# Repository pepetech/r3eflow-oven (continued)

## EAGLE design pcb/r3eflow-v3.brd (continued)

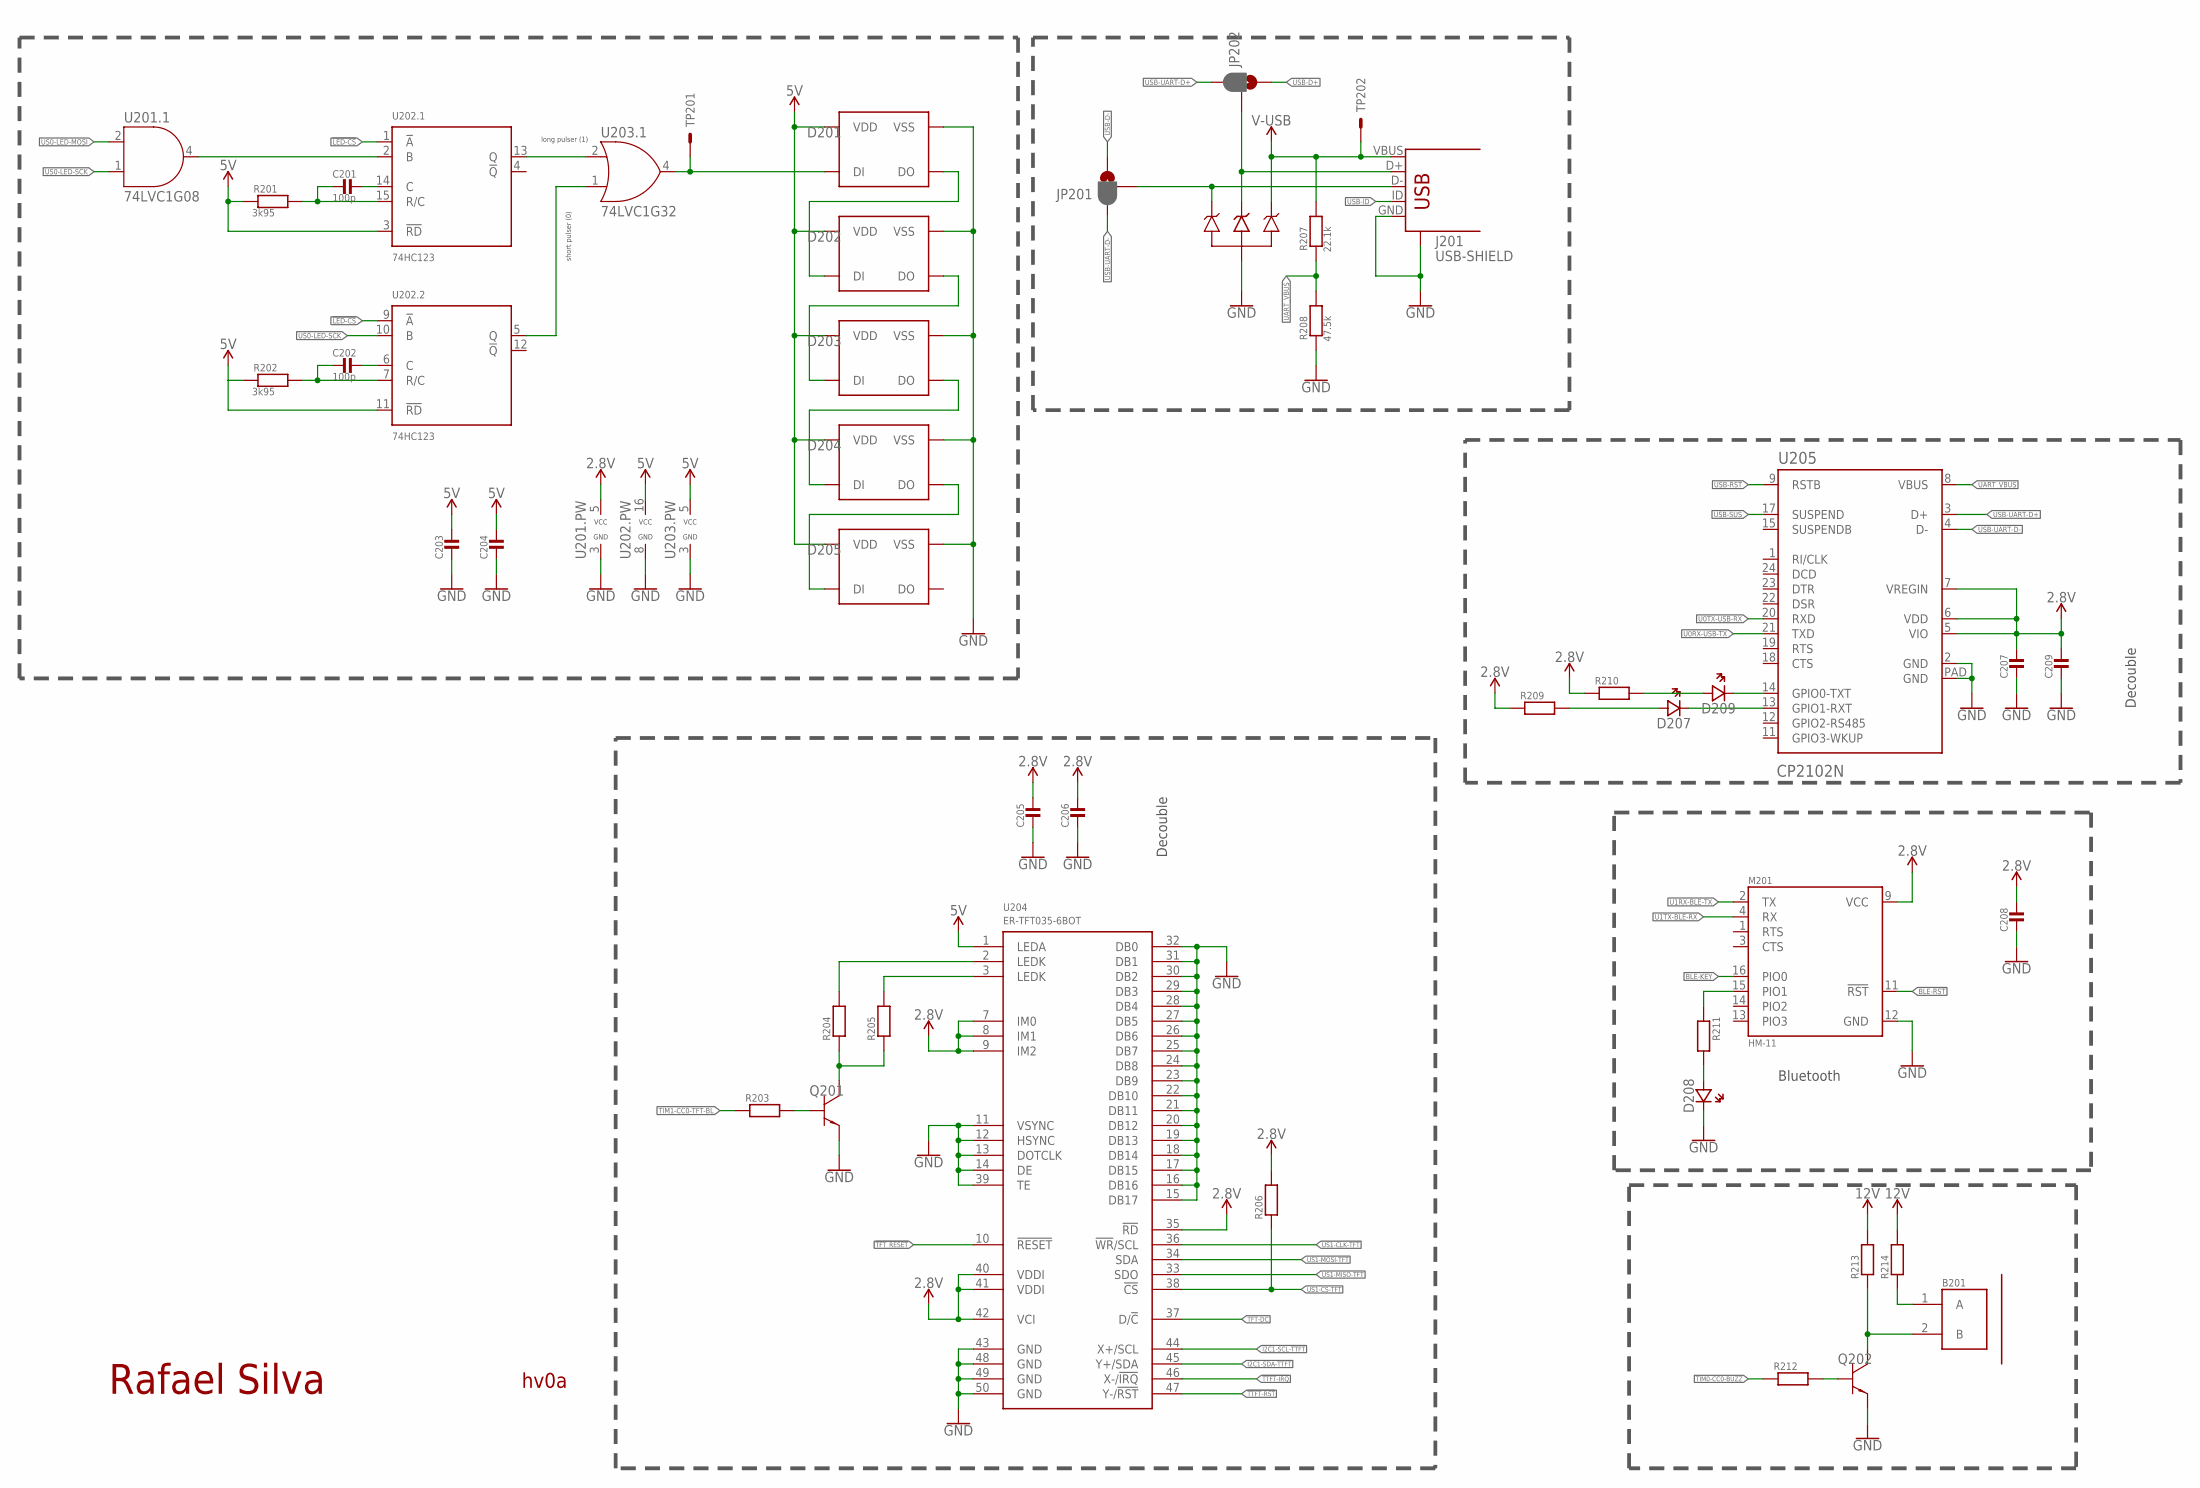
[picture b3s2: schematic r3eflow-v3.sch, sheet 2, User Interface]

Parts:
B201: PKLCS1212E2400-R1; BUZZ_PIEZO_SMD
C201, C202: 100p; 0603_WAVE
C203, C204, C205, C206, C207, C208, C209: MLCC0603; 0603_WAVE
D201, D202, D203, D204, D205: WS2812B; 3535
D206: SP0503BAHT; SOT143
D207, D208, D209: LED0603; CHIPLED_0603
J201: USB-SHIELD; USB-M-S1
JP201, JP202: JUMPER-SMT_3_1-NC_PASTE_SILK; SMT-JUMPER_3_1-NC_PASTE_SILK
M201: HM-11
Q201, Q202: BC817-40; SOT-23-3
R201, R202: 3k95; 0603_WAVE
R203, R204, R205, R206, R209, R210, R211, R212, R213, R214: RESISTOR0603; 0603_WAVE
R207: 22.1k; 0603_WAVE
R208: 47.5k; 0603_WAVE
TP201, TP202: TEST_POINT
U201: 74LVC1G08; SC-70-5
U202: 74HC123; TSSOP-16
U203: 74LVC1G32; SC-70-5
U204: ER-TFT035-6BOT; ZIF50-TFT_BACK
U205: CP2102N; QFN24

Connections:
2.8V: C205.P$1, C206.P$1, C207.P$1, C208.P$1, C209.P$1, M201.9 (VCC), R206.P$2, R209.P$1, R210.P$1, U201.5 (VCC), U204.7 (IM0), U204.8 (IM1), U204.9 (IM2), U204.35 (!RD), U204.40 (VDDI), U204.41 (VDDI), U204.42 (VCI), U205.5 (VIO), U205.6 (VDD), U205.7 (VREGIN); also elsewhere on the board
5V: C203.P$1, C204.P$1, D201.3 (VDD), D202.3 (VDD), D203.3 (VDD), D204.3 (VDD), D205.3 (VDD), R201.P$1, R202.P$1, U202.3 (!RD), U202.11 (!RD), U202.16 (VCC), U203.5 (VCC), U204.1 (LEDA); also elsewhere on the board
12V: R213.P$2, R214.P$2; also elsewhere on the board
!LED-CS: U202.1 (!A), U202.9 (!A); also elsewhere on the board
!TFT_RESET: U204.10 (!RESET); also elsewhere on the board
!TTFT-IRQ: U204.46 (X-/!IRQ!); also elsewhere on the board
!TTFT-RST: U204.47 (Y-/!RST!); also elsewhere on the board
BLE-!RST: M201.11 (!RST!); also elsewhere on the board
BLE-KEY: M201.16 (PIO0); also elsewhere on the board
D8-DI: D201.2 (DI), TP201.1, U203.4 (Y)
D8_DO: D201.4 (DO), D202.2 (DI)
D9-DO: D202.4 (DO), D203.2 (DI)
D10-DO: D203.4 (DO), D204.2 (DI)
D11-DO: D204.4 (DO), D205.2 (DI)
GND: C203.P$2, C204.P$2, C205.P$2, C206.P$2, C207.P$2, C208.P$2, C209.P$2, D201.1 (VSS), D202.1 (VSS), D203.1 (VSS), D204.1 (VSS), D205.1 (VSS), D206.1, D208.C (CA), J201.GND, J201.GND@1 (CASE), J201.GND@2 (CASE), J201.GND@3 (CASE), J201.GND@4 (CASE), M201.12 (GND), Q201.P$2 (EM2), Q202.P$2 (EM2), R208.P$1, U201.3 (GND), U202.8 (GND), U203.3 (GND), U204.11 (VSYNC), U204.12 (HSYNC), U204.13 (DOTCLK), U204.14 (DE), U204.15 (DB17), U204.16 (DB16), U204.17 (DB15), U204.18 (DB14), U204.19 (DB13), U204.20 (DB12), U204.21 (DB11), U204.22 (DB10), U204.23 (DB9), U204.24 (DB8), U204.25 (DB7), U204.26 (DB6), U204.27 (DB5), U204.28 (DB4), U204.29 (DB3), U204.30 (DB2), U204.31 (DB1), U204.32 (DB0), U204.39 (TE), U204.43 (GND), U204.48 (GND), U204.49 (GND), U204.50 (GND), U205.2 (GND), U205.PAD (GND); also elsewhere on the board
I2C1-SCL-TTFT: U204.44 (X+/SCL); also elsewhere on the board
I2C1-SDA-TTFT: U204.45 (Y+/SDA); also elsewhere on the board
unnamed: B201.1 (A), R214.P$1
unnamed: D207.C (CA), U205.13 (GPIO1-RXT)
unnamed: D209.C (CA), U205.14 (GPIO0-TXT)
unnamed: D209.A (AN), R210.P$2
unnamed: B201.2 (B), Q202.P$3 (C03), R213.P$1
unnamed: Q202.P$1 (BA1), R212.P$2
unnamed: D207.A (AN), R209.P$2
unnamed: Q201.P$1 (BA1), R203.P$2
unnamed: D208.A (AN), R211.P$2
unnamed: M201.15 (PIO1), R211.P$1
unnamed: U202.5 (Q), U203.1 (B)
unnamed: U202.13 (Q), U203.2 (A)
unnamed: U201.4 (Y), U202.2 (B)
unnamed: D206.3, J201.D+, JP202.2
unnamed: D206.2, J201.D-, JP201.2
TFT-DC: U204.37 (D/!C!); also elsewhere on the board
TFT-LEDK: Q201.P$3 (C03), R204.P$1, R205.P$1
TFT-LEDK1: R204.P$2, U204.2 (LEDK)
TFT-LEDK2: R205.P$2, U204.3 (LEDK)
TIM0-CC0-BUZZ: R212.P$1; also elsewhere on the board
TIM1-CC0-TFT-BL: R203.P$1; also elsewhere on the board
U0RX-USB-TX: U205.21 (TXD); also elsewhere on the board
U0TX-USB-RX: U205.20 (RXD); also elsewhere on the board
U1RX-BLE-TX: M201.2 (TX); also elsewhere on the board
U1TX-BLE-RX: M201.4 (RX); also elsewhere on the board
U11.1-C: C201.P$1, U202.14 (C)
U11.1-RC: C201.P$2, R201.P$2, U202.15 (R/C)
U11.2-C: C202.P$1, U202.6 (C)
U11.2-RC: C202.P$2, R202.P$2, U202.7 (R/C)
UART_VBUS: R207.P$1, R208.P$2, U205.8 (VBUS)
US0-LED-MOSI: U201.2 (A); also elsewhere on the board
US0-LED-SCK: U201.1 (B), U202.10 (B); also elsewhere on the board
US1-CLK-TFT: U204.36 (!WR!/SCL); also elsewhere on the board
US1-CS-TFT: R206.P$1, U204.38 (!CS); also elsewhere on the board
US1-MISO-TFT: U204.33 (SDO); also elsewhere on the board
US1-MOSI-TFT: U204.34 (SDA); also elsewhere on the board
USB-D+: JP202.1; also elsewhere on the board
USB-D-: JP201.1; also elsewhere on the board
USB-ID: J201.ID; also elsewhere on the board
USB-RST: U205.9 (RSTB); also elsewhere on the board
USB-SUS: U205.17 (SUSPEND); also elsewhere on the board
USB-UART-D+: JP202.3, U205.3 (D+)
USB-UART-D-: JP201.3, U205.4 (D-)
V_USB: D206.4, J201.VBUS, R207.P$2, TP202.1

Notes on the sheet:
Decouble
Bluetooth
short pulser (0)
long pulser (1)

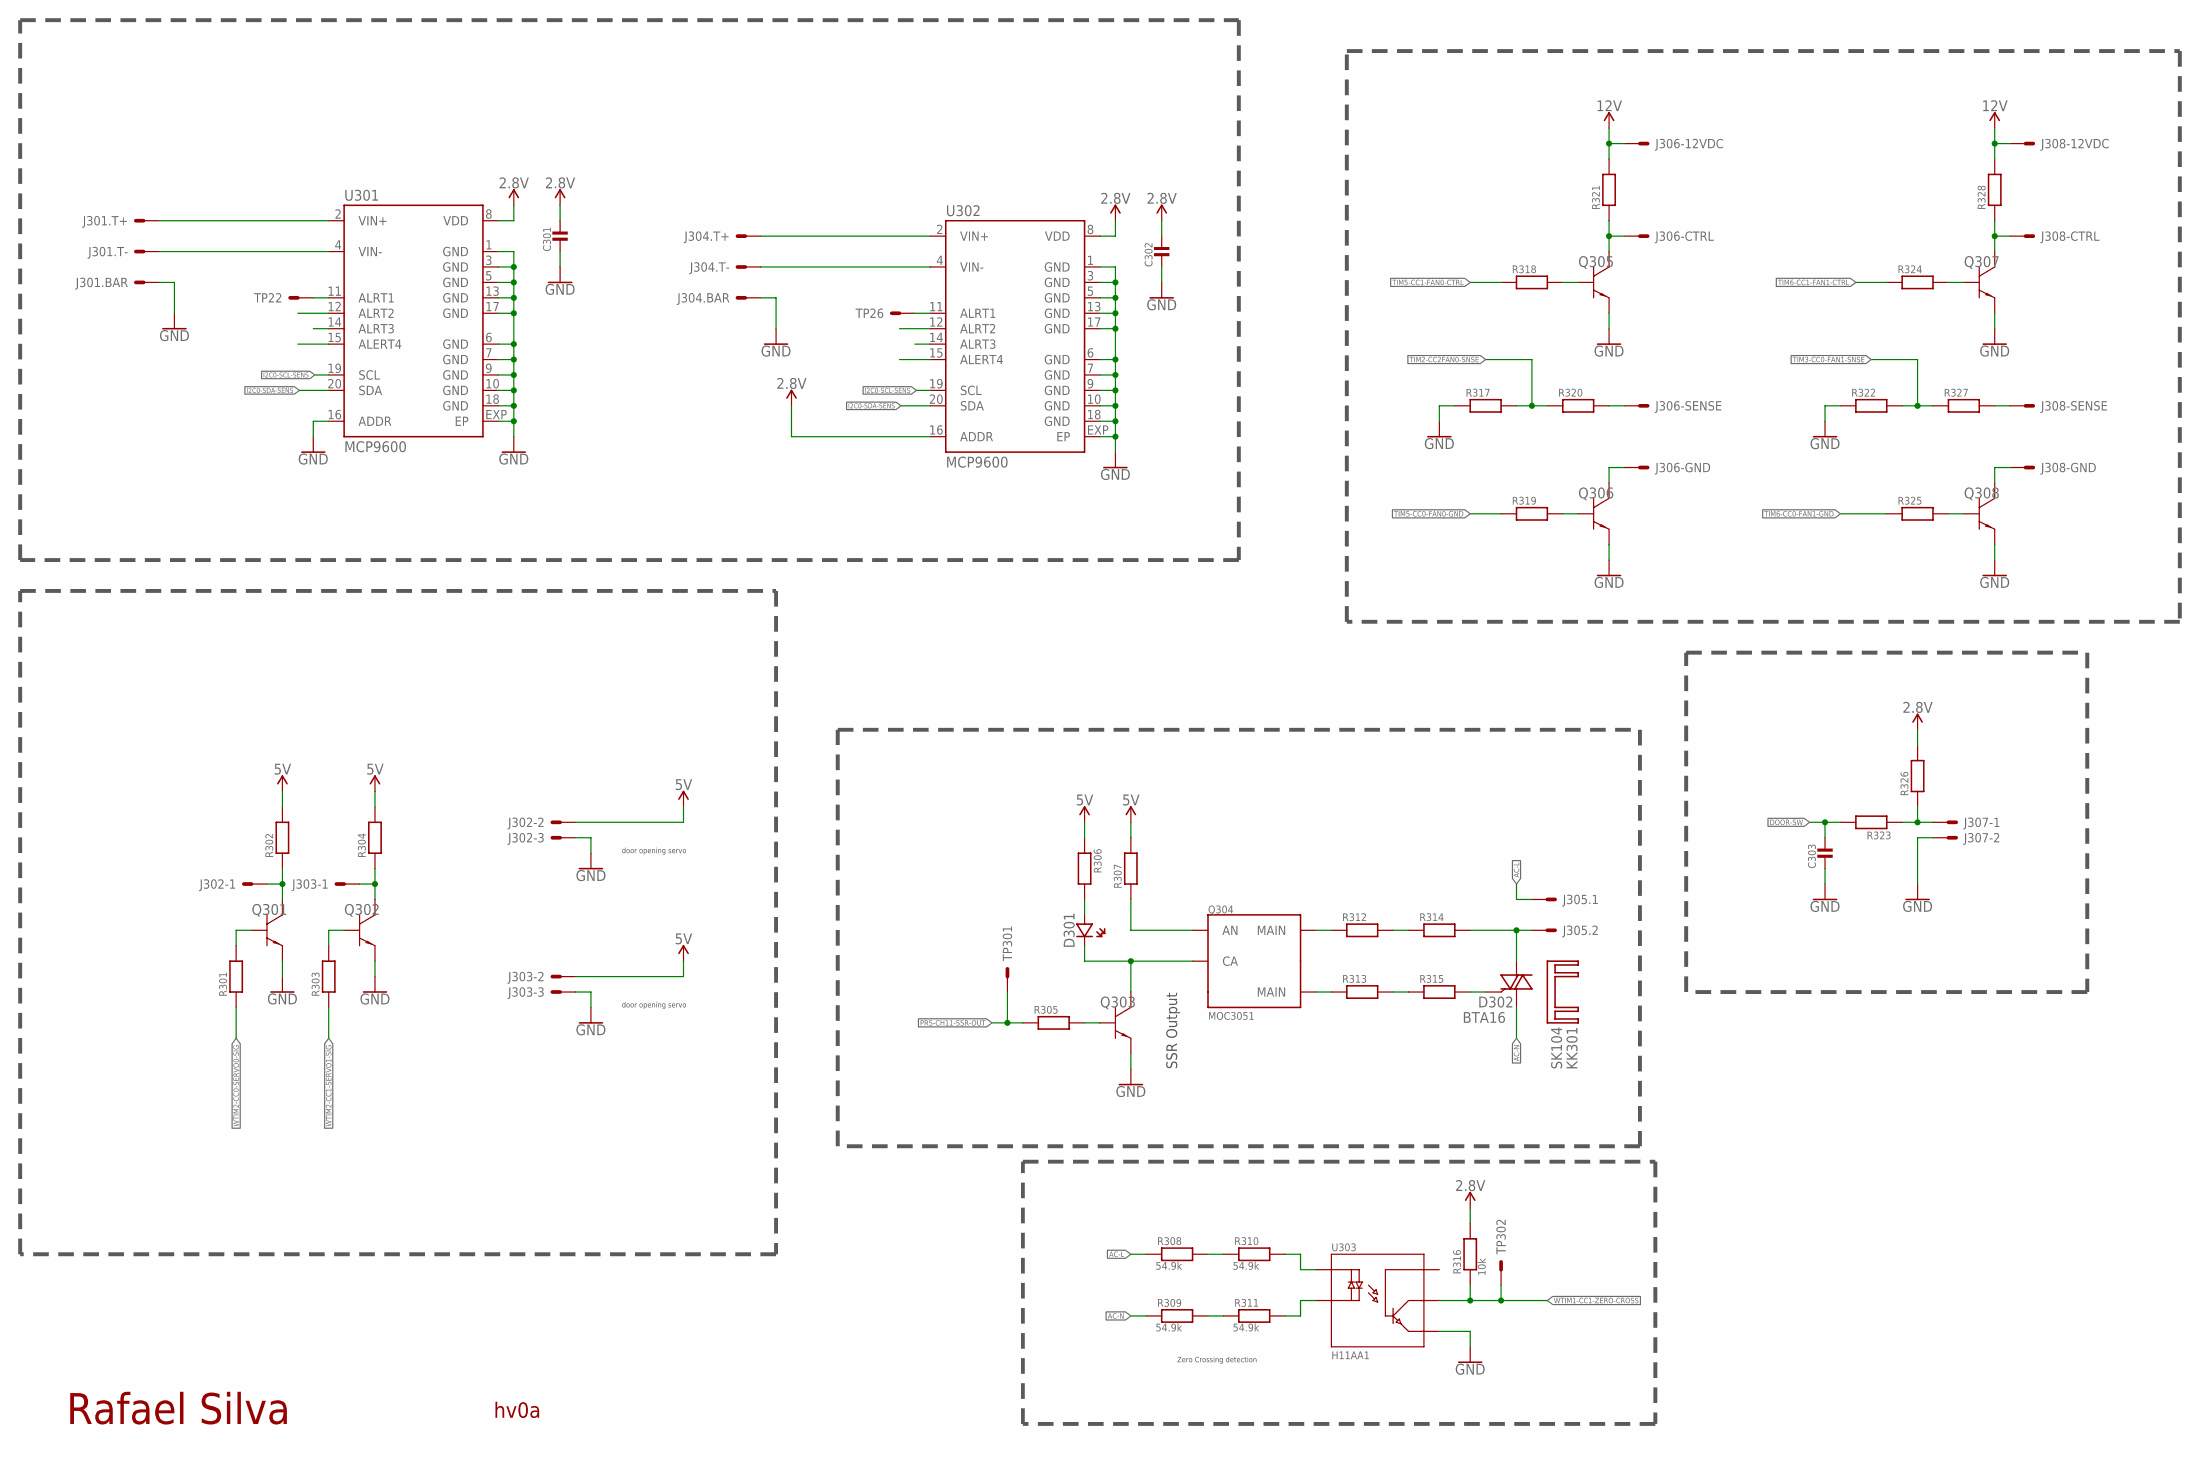
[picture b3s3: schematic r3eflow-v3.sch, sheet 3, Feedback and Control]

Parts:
C301, C302, C303: MLCC0603; 0603_WAVE
D301: LED0603; CHIPLED_0603
D302: BTA16; TO220DS
J301, J304: PCC-SMP
J302, J303: 3X1_2.54
J305: 2EDG-2P
J306, J308: 4P-PC-FAN; KF2510-3+1P
J307: 2X1_2.54
KK301: SK104
Q301, Q302, Q303, Q305, Q306, Q307, Q308: BC817-40; SOT-23-3
Q304: MOC3051; DIP-6-SMD
R301, R302, R303, R304, R305, R306, R307, R317, R318, R319, R320, R321, R322, R323, R324, R325, R326, R327, R328: RESISTOR0603; 0603_WAVE
R308, R309, R310, R311: 54.9k; _1206
R312, R313, R314, R315: RESISTOR_1206; _1206
R316: 10k; 0603_WAVE
TP22, TP26, TP301, TP302: TEST_POINT
U301, U302: MCP9600; TQFN20-5X5
U303: H11AA1; DIP-6-SMD

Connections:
2.8V: C301.P$1, C302.P$1, R316.P$2, R326.P$2, U301.8 (VDD), U302.8 (VDD), U302.16 (ADDR); also elsewhere on the board
5V: J302.P$2, J303.P$2, R302.P$2, R304.P$2, R306.P$1, R307.P$2; also elsewhere on the board
12V: J306.2, J308.2, R321.P$2, R328.P$2; also elsewhere on the board
AC-L: J305.P$1, R308.1; also elsewhere on the board
AC-N: D302.A1, R309.1; also elsewhere on the board
DOOR-SW: C303.P$1, R323.P$2; also elsewhere on the board
GND: C301.P$2, C302.P$2, C303.P$2, J301.3-BAR, J301.4-BAR, J302.P$3, J303.P$3, J304.3-BAR, J304.4-BAR, J307.2, Q301.P$2 (EM2), Q302.P$2 (EM2), Q303.P$2 (EM2), Q305.P$2 (EM2), Q306.P$2 (EM2), Q307.P$2 (EM2), Q308.P$2 (EM2), R317.P$1, R322.P$1, U301.1 (GND), U301.3 (GND), U301.5 (GND), U301.6 (GND), U301.7 (GND), U301.9 (GND), U301.10 (GND), U301.13 (GND), U301.16 (ADDR), U301.17 (GND), U301.18 (GND), U301.EXP (EP), U302.1 (GND), U302.3 (GND), U302.5 (GND), U302.6 (GND), U302.7 (GND), U302.9 (GND), U302.10 (GND), U302.13 (GND), U302.17 (GND), U302.18 (GND), U302.EXP (EP), U303.P$4 (E); also elsewhere on the board
I2C0-SCL-SENS: U301.19 (SCL), U302.19 (SCL); also elsewhere on the board
I2C0-SDA-SENS: U301.20 (SDA), U302.20 (SDA); also elsewhere on the board
unnamed: J307.1, R323.P$1, R326.P$1
unnamed: D302.A2, J305.P$2, R314.2
unnamed: Q303.P$1 (BA1), R305.P$2
unnamed: D301.C (CA), Q303.P$3 (C03), Q304.P$2 (CA)
unnamed: R308.2, R310.1
unnamed: R310.2, U303.P$1 (AC)
unnamed: R311.2, U303.P$2 (CA)
unnamed: R309.2, R311.1
unnamed: Q304.P$1 (AN), R307.P$1
unnamed: Q304.P$4 (MAIN), R312.1
unnamed: Q304.P$6 (MAIN), R313.1
unnamed: R312.2, R314.1
unnamed: R313.2, R315.1
unnamed: D302.G, R315.2
unnamed: Q301.P$1 (BA1), R301.P$2
unnamed: J302.P$1, Q301.P$3 (C03), R302.P$1
unnamed: D301.A (AN), R306.P$2
unnamed: J303.P$1, Q302.P$3 (C03), R304.P$1
unnamed: Q302.P$1 (BA1), R303.P$2
unnamed: Q306.P$1 (BA1), R319.P$2
unnamed: J306.1, Q306.P$3 (C03)
unnamed: Q305.P$1 (BA1), R318.P$2
unnamed: J306.4, Q305.P$3 (C03), R321.P$1
unnamed: Q308.P$1 (BA1), R325.P$2
unnamed: Q307.P$1 (BA1), R324.P$2
unnamed: J308.4, Q307.P$3 (C03), R328.P$1
unnamed: J308.1, Q308.P$3 (C03)
unnamed: J306.3, R320.P$2
unnamed: J308.3, R327.P$2
PRS-CH11-SSR-OUT: R305.P$1, TP301.1; also elsewhere on the board
TC_VIN0+: J301.1-T+, U301.2 (VIN+)
TC_VIN0-: J301.2-T-, U301.4 (VIN-)
TC_VIN1+: J304.1-T+, U302.2 (VIN+)
TC_VIN1-: J304.2-T-, U302.4 (VIN-)
TIM2-CC2FAN0-SNSE: R317.P$2, R320.P$1; also elsewhere on the board
TIM3-CC0-FAN1-SNSE: R322.P$2, R327.P$1; also elsewhere on the board
TIM5-CC0-FAN0-GND: R319.P$1; also elsewhere on the board
TIM5-CC1-FAN0-CTRL: R318.P$1; also elsewhere on the board
TIM6-CC0-FAN1-GND: R325.P$1; also elsewhere on the board
TIM6-CC1-FAN1-CTRL: R324.P$1; also elsewhere on the board
U4-ALRT1: TP22.1, U301.11 (ALRT1)
U4-ALRT2: U301.12 (ALRT2)
U4-ALRT3: U301.14 (ALRT3)
U4-ALRT4: U301.15 (ALERT4)
U7-ALRT1: TP26.1, U302.11 (ALRT1)
U7-ALRT2: U302.12 (ALRT2)
U7-ALRT3: U302.14 (ALRT3)
U7-ALRT4: U302.15 (ALERT4)
WTIM1-CC1-ZERO-CROSS: R316.P$1, TP302.1, U303.P$5 (C); also elsewhere on the board
WTIM2-CC0-SERVO0-SIG: R301.P$1; also elsewhere on the board
WTIM2-CC1-SERVO1-SIG: R303.P$1; also elsewhere on the board

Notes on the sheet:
SSR Output
Zero Crossing detection
door opening servo

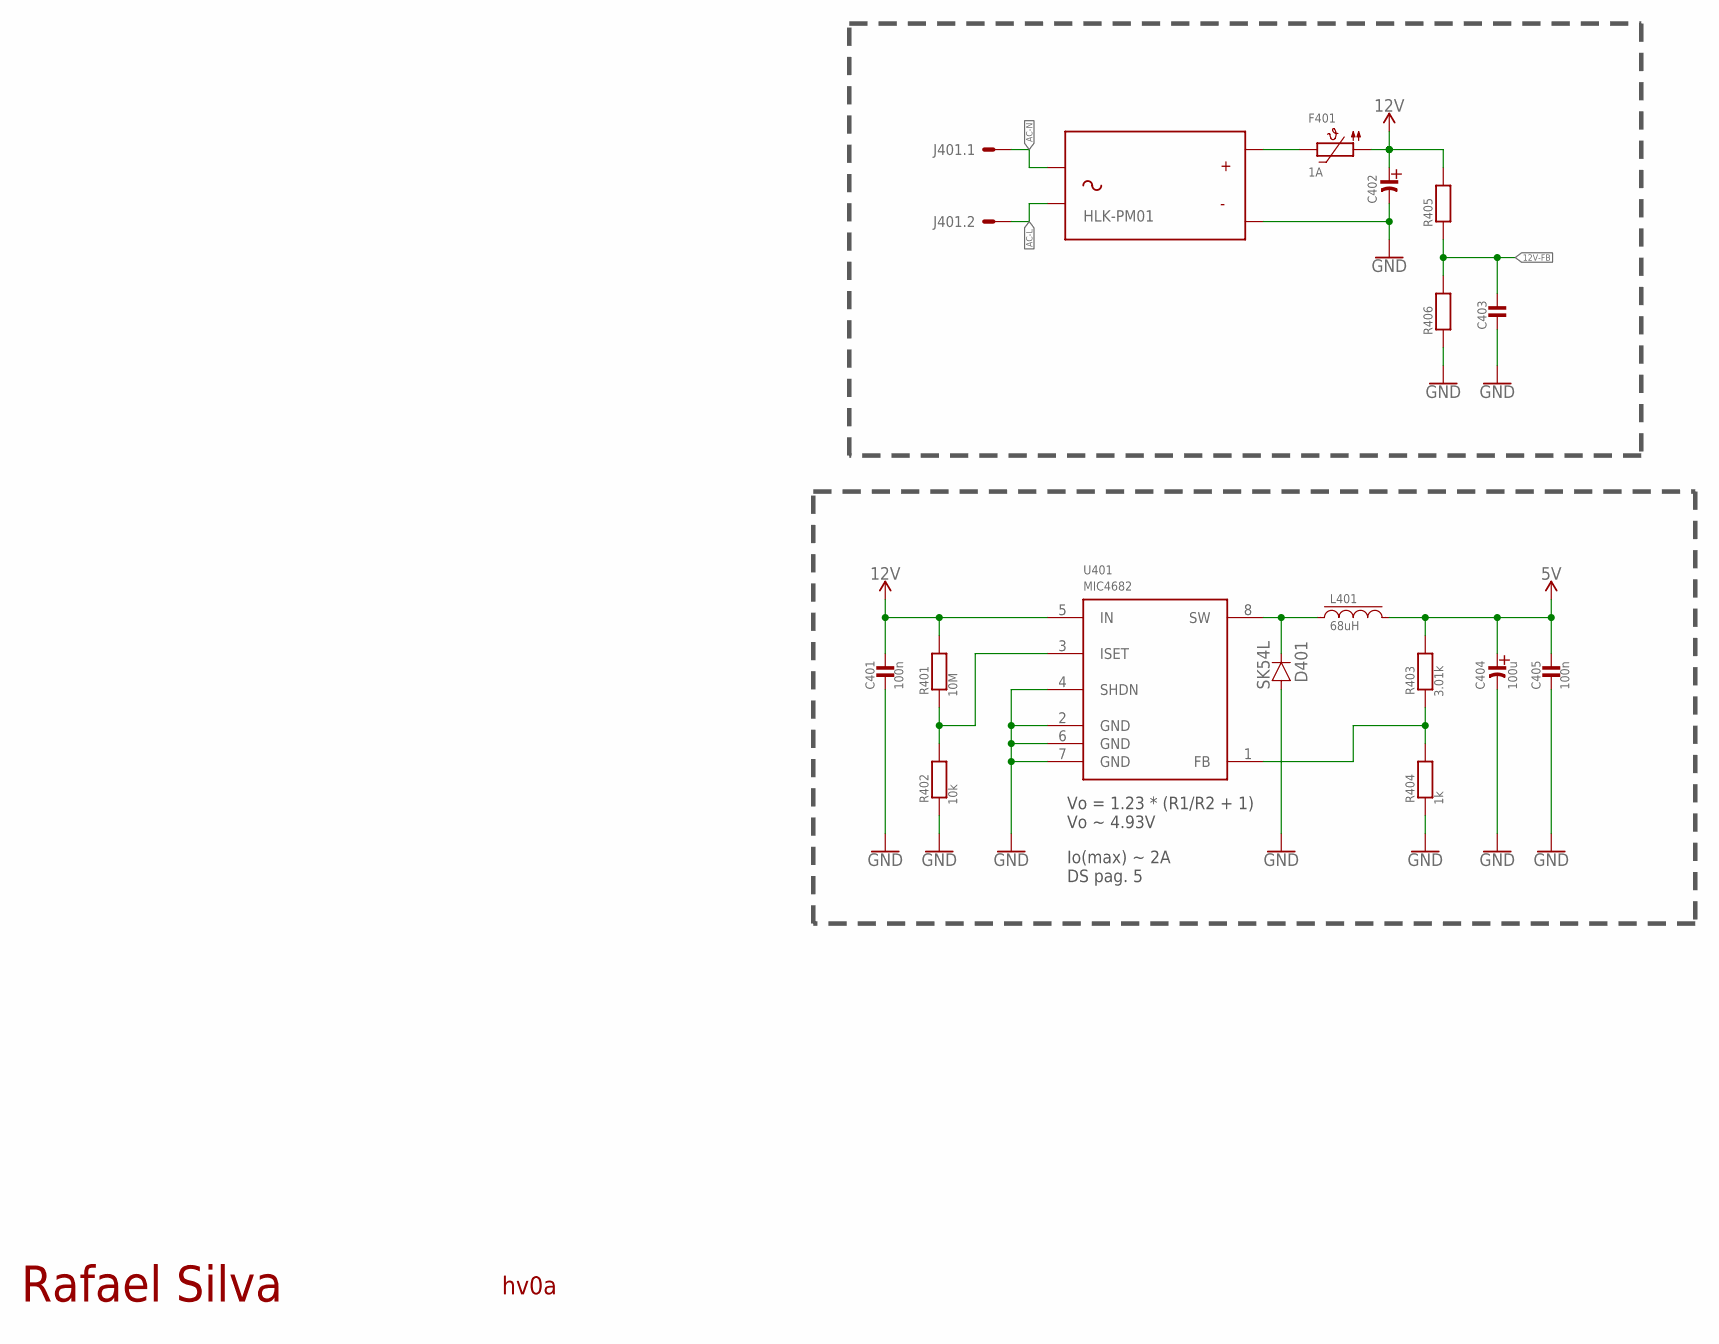
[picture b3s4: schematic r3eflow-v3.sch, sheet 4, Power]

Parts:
ACDC401: HLK-PM01
C401, C405: 100n; 0603_WAVE
C402: CAPACITOR_ELD; PANASONIC_D
C403: MLCC0603; 0603_WAVE
C404: 100u; PANASONIC_D
D401: SK54L; DO214AA
F401: 1A; PTC1812
J401: 2EDG-2P
L401: 68uH; 1207
R401: 10M; 0603_WAVE
R402: 10k; 0603_WAVE
R403: 3.01k; 0603_WAVE
R404: 1k; 0603_WAVE
R405, R406: RESISTOR0603; 0603_WAVE
U401: MIC4682; SOIC8

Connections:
5V: C404.+ (AN), C405.P$1, L401.2, R403.P$2; also elsewhere on the board
5V-FB: R403.P$1, R404.P$2, U401.1 (FB)
12V: C401.P$1, C402.+ (AN), F401.P$1 (1), R401.P$2, R405.P$2, U401.5 (IN); also elsewhere on the board
12V-FB: C403.P$1, R405.P$1, R406.P$2; also elsewhere on the board
AC-L: ACDC401.AC2, J401.P$2; also elsewhere on the board
AC-N: ACDC401.AC1, J401.P$1; also elsewhere on the board
GND: ACDC401.-VO, C401.P$2, C402.- (CA), C403.P$2, C404.- (CA), C405.P$2, D401.A, R402.P$1, R404.P$1, R406.P$1, U401.2 (GND), U401.4 (SHDN), U401.6 (GND), U401.7 (GND); also elsewhere on the board
unnamed: ACDC401.+VO, F401.P$2 (2)
unnamed: D401.C, L401.1, U401.8 (SW)
unnamed: R401.P$1, R402.P$2, U401.3 (ISET)

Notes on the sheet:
Vo = 1.23 * (R1/R2 + 1) Vo ~ 4.93V
Io(max) ~ 2A DS pag. 5

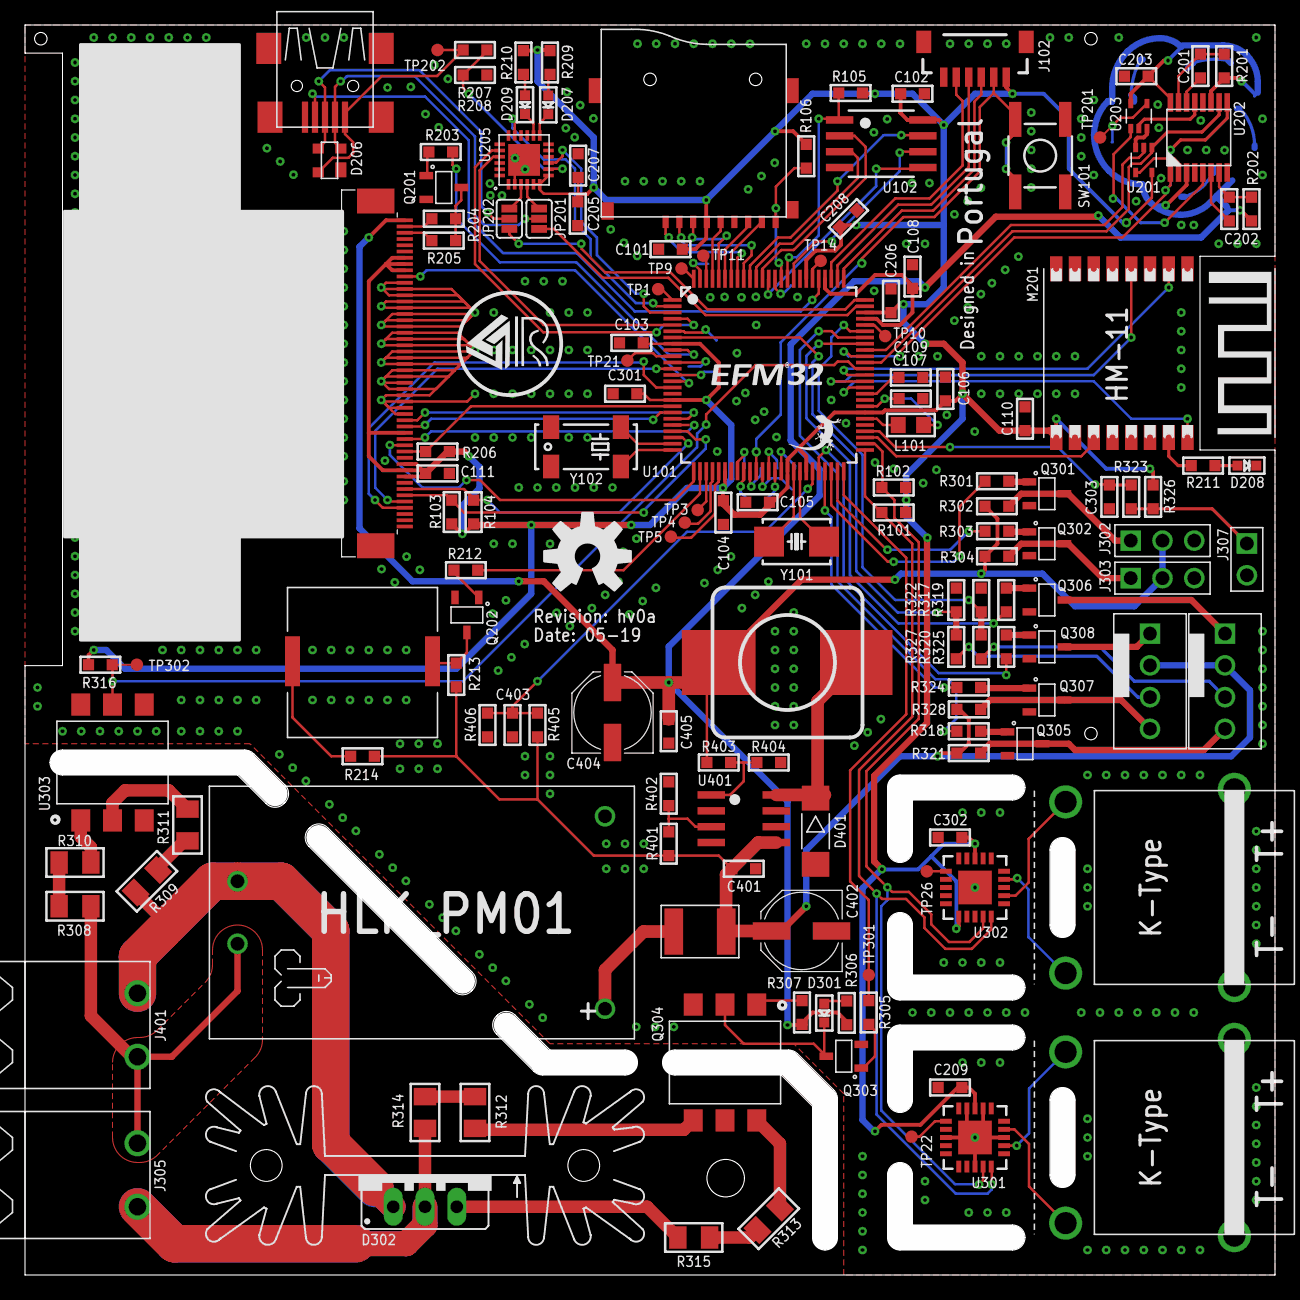
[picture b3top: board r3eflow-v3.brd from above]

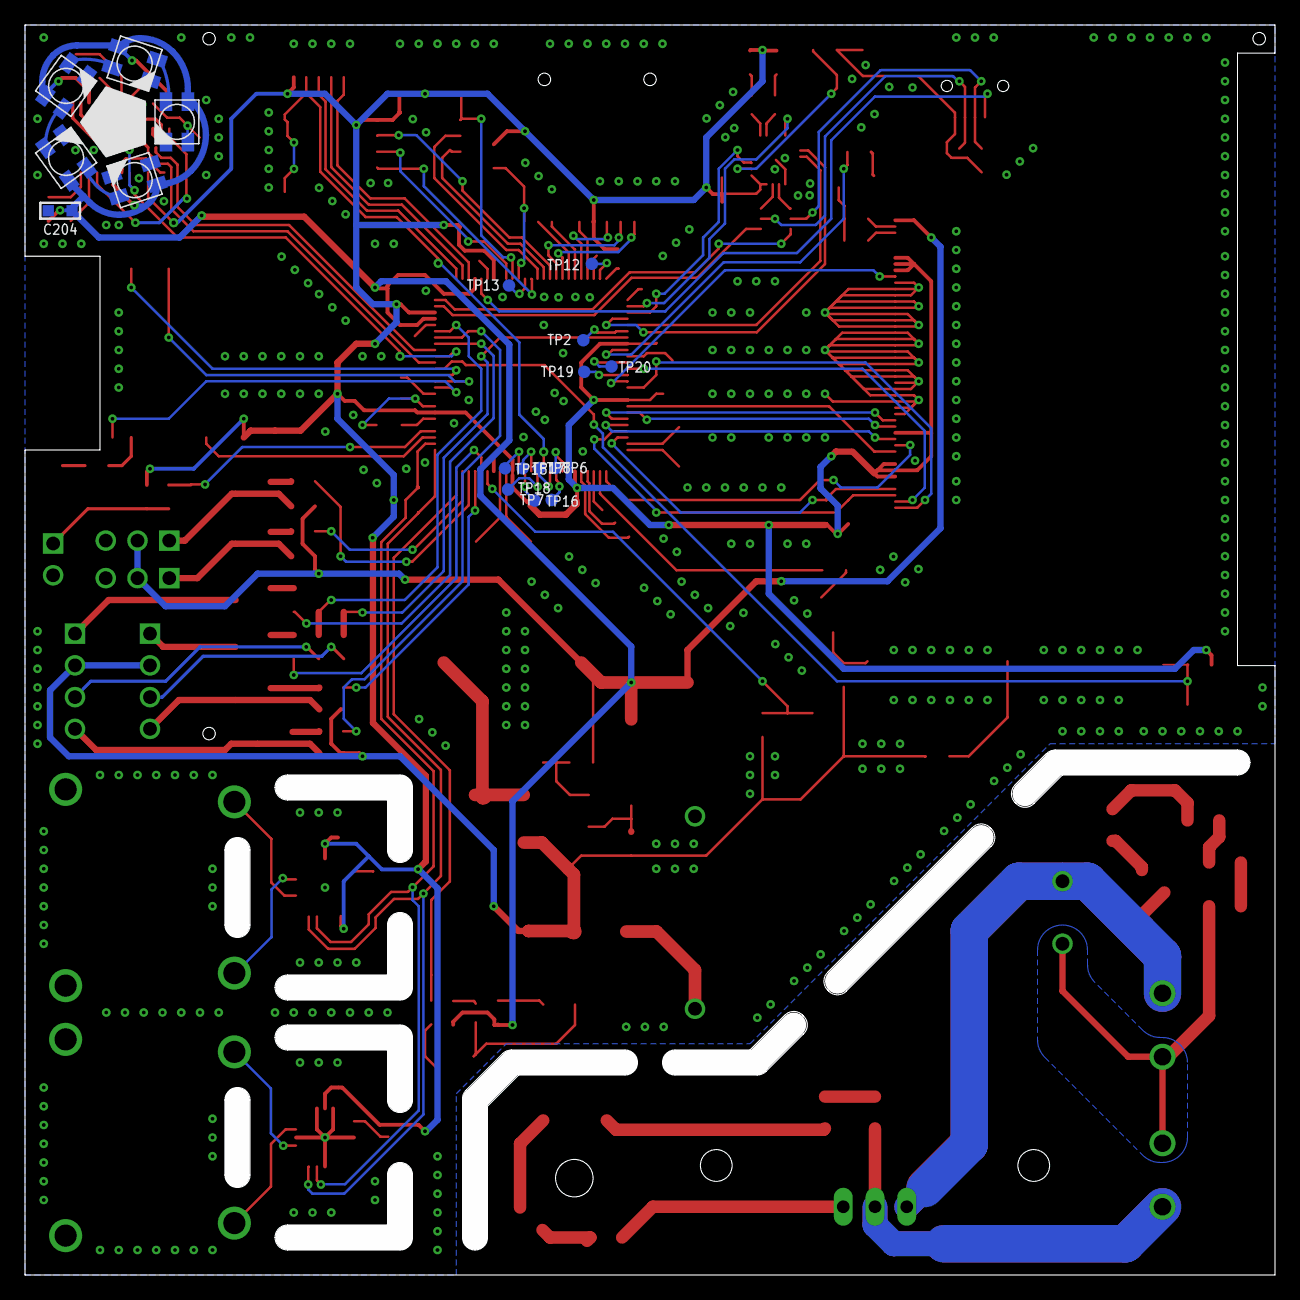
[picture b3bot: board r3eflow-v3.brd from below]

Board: 2 copper layers, 100.0 x 100.0 mm, 169 parts (19 on the bottom side), 161 nets.
